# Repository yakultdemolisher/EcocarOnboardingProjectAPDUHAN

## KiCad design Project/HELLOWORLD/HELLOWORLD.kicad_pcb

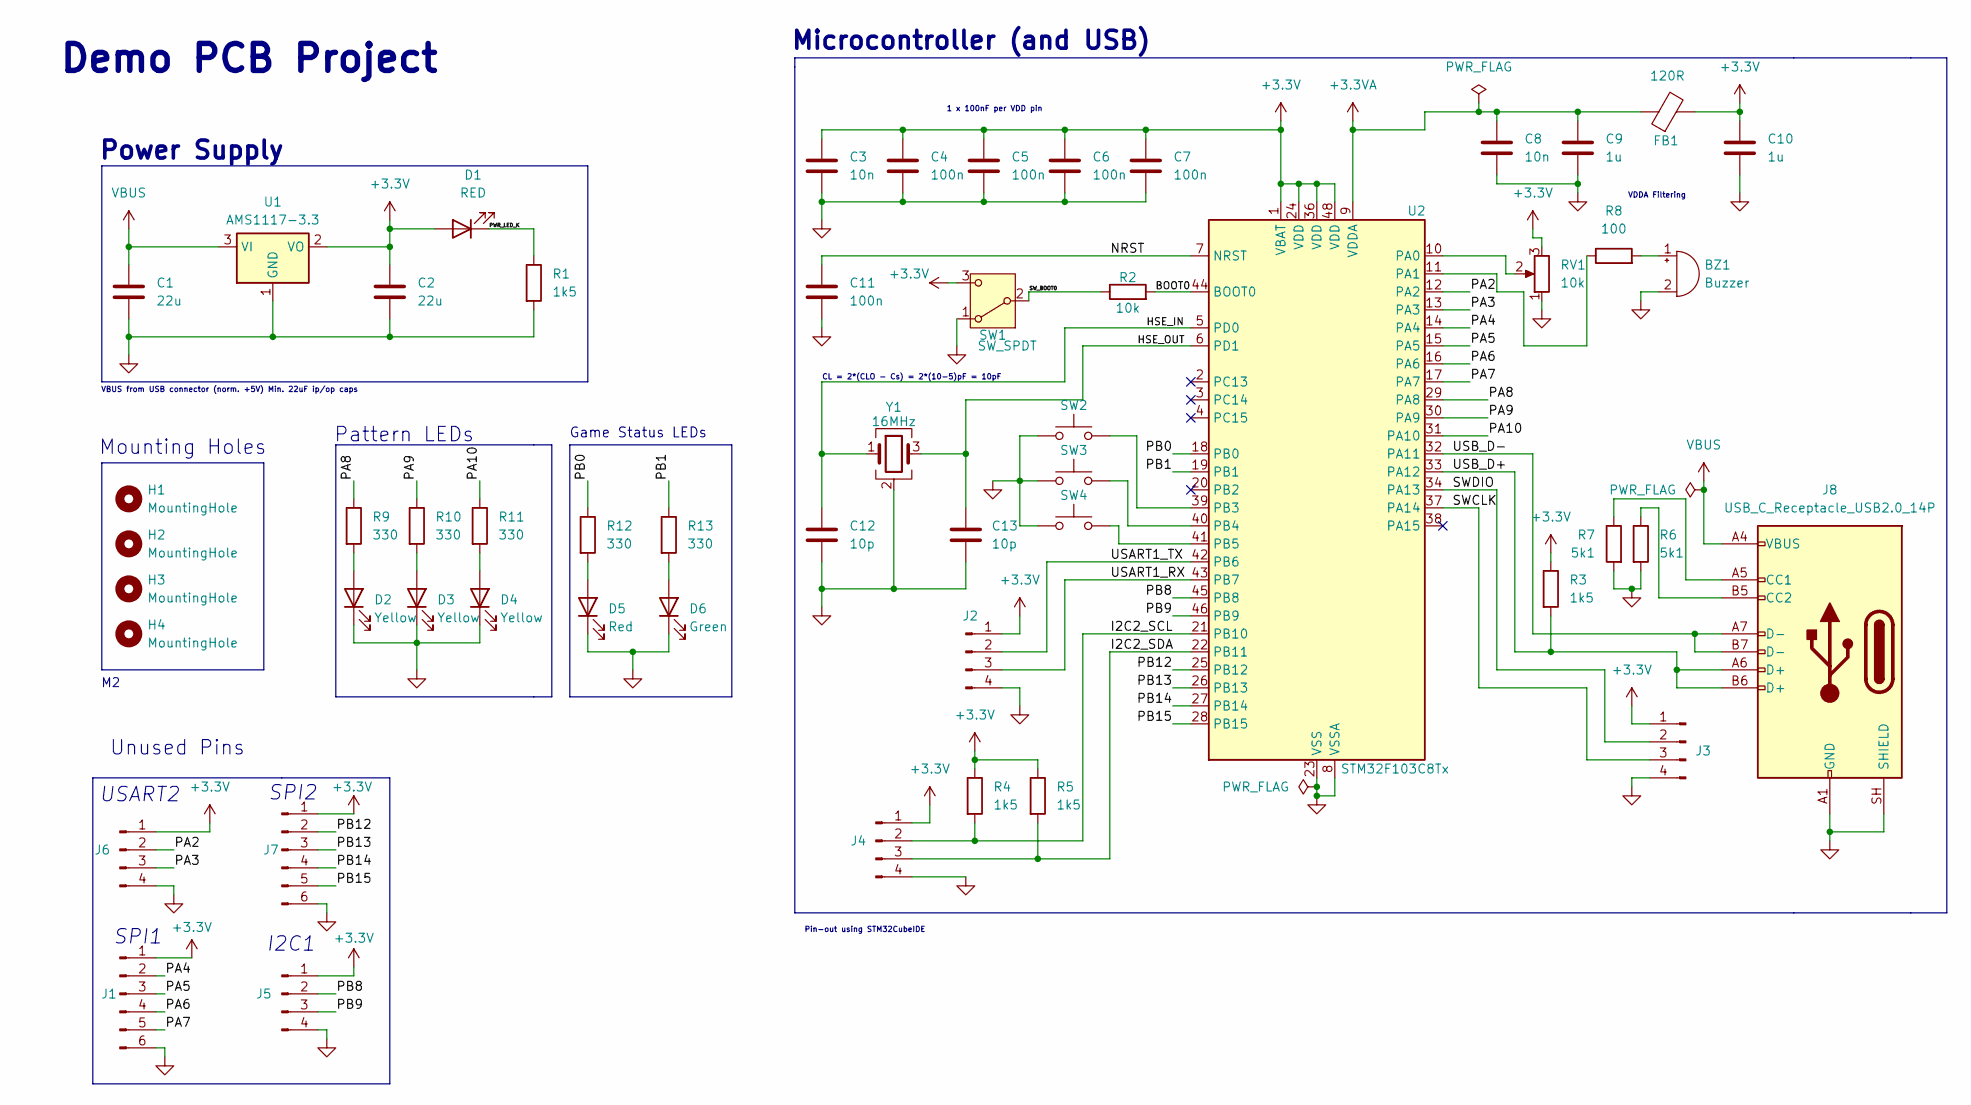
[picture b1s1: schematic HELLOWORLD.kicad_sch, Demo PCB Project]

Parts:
BZ1: Buzzer; Buzzer_12x9.5RM7.6
C1, C2: 22u; C_0805_2012Metric
C3, C8: 10n; C_0603_1608Metric
C4, C5, C6, C7, C11: 100n; C_0603_1608Metric
C9, C10: 1u; C_0603_1608Metric
C12, C13: 10p; C_0603_1608Metric
D1: RED; LED_0603_1608Metric
D2, D3, D4: Yellow; LED_0603_1608Metric
D5: Red; LED_0603_1608Metric
D6: Green; LED_0603_1608Metric
FB1: 120R; L_0603_1608Metric
H1, H2, H3, H4: MountingHole; MountingHole_2.2mm_M2
J1, J7: Conn_01x06_Pin; PinHeader_1x06_P2.54mm_Vertical
J2, J3, J4, J5, J6: Conn_01x04_Pin; PinHeader_1x04_P2.54mm_Vertical
J8: USB_C_Receptacle_USB2.0_14P; USB_C_Receptacle_GCT_USB4105-xx-A_16P_TopMnt_Horizontal
R1, R3, R4, R5: 1k5; R_0603_1608Metric
R2: 10k; R_0603_1608Metric
R6, R7: 5k1; R_0603_1608Metric
R8: 100; R_0603_1608Metric
R9, R10, R11, R12, R13: 330; R_0603_1608Metric
RV1: 10k; Potentiometer_Alps_RK09K_Single_Vertical
SW1: SW_SPDT; SW_SPDT_PCM12
SW2, SW3, SW4: SW_Push; SW_PUSH_6mm
U1: AMS1117-3.3; SOT-223-3_TabPin2
U2: STM32F103C8Tx; LQFP-48_7x7mm_P0.5mm
Y1: 16MHz; Crystal_SMD_3225-4Pin_3.2x2.5mm

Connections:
+3.3V: C2.1, C3.1, C4.1, C5.1, C6.1, C7.1, C10.1, D1.2 (A), FB1.2, J1.1, J2.1, J3.1, J4.1, J5.1, J6.1, J7.1, R3.1, R4.1, R5.1, RV1.3, SW1.3 (C), U1.2 (VO), U2.1 (VBAT), U2.24 (VDD), U2.36 (VDD), U2.48 (VDD)
+3.3VA: C8.1, C9.1, FB1.1, U2.9 (VDDA)
/BOOT0: R2.2, U2.44 (BOOT0)
/HSE_IN: C12.1, U2.5 (PD0), Y1.1
/HSE_OUT: C13.1, U2.6 (PD1), Y1.3
/I2C2_SCL: J4.2, R4.2, U2.21 (PB10)
/I2C2_SDA: J4.3, R5.2, U2.22 (PB11)
/NRST: C11.1, U2.7 (NRST)
/PA2: J6.2, U2.12 (PA2)
/PA3: J6.3, U2.13 (PA3)
/PA4: J1.2, U2.14 (PA4)
/PA5: J1.3, U2.15 (PA5)
/PA6: J1.4, U2.16 (PA6)
/PA7: J1.5, U2.17 (PA7)
/PA8: R9.1, U2.29 (PA8)
/PA9: R10.1, U2.30 (PA9)
/PA10: R11.1, U2.31 (PA10)
/PB0: R12.1, U2.18 (PB0)
/PB1: R13.1, U2.19 (PB1)
/PB8: J5.2, U2.45 (PB8)
/PB9: J5.3, U2.46 (PB9)
/PB12: J7.2, U2.25 (PB12)
/PB13: J7.3, U2.26 (PB13)
/PB14: J7.4, U2.27 (PB14)
/PB15: J7.5, U2.28 (PB15)
/PWR_LED_K: D1.1 (K), R1.1
/SWCLK: J3.3, U2.37 (PA14)
/SWDIO: J3.2, U2.34 (PA13)
/SW_BOOT0: R2.1, SW1.2 (B)
/USART1_RX: J2.3, U2.43 (PB7)
/USART1_TX: J2.2, U2.42 (PB6)
/USB_D+: J8.A6 (D+), J8.B6 (D+), R3.2, U2.33 (PA12)
/USB_D-: J8.A7 (D-), J8.B7 (D-), U2.32 (PA11)
GND: BZ1.2 (-), C1.2, C2.2, C3.2, C4.2, C5.2, C6.2, C7.2, C8.2, C9.2, C10.2, C11.2, C12.2, C13.2, D2.1 (K), D3.1 (K), D4.1 (K), D5.1 (K), D6.1 (K), J1.6, J2.4, J3.4, J4.4, J5.4, J6.4, J7.6, J8.A1 (GND), J8.A12 (GND), J8.B1 (GND), J8.B12 (GND), J8.SH (SHIELD), R1.2, R6.2, R7.2, RV1.1, SW1.1 (A), SW2.1, SW3.1, SW4.1, U1.1 (GND), U2.8 (VSSA), U2.23 (VSS), U2.35 (VSS), U2.47 (VSS), Y1.2 (G), Y1.4 (G)
unnamed: BZ1.1 (+), R8.2
unnamed: D2.2 (A), R9.2
unnamed: D3.2 (A), R10.2
unnamed: D4.2 (A), R11.2
unnamed: D5.2 (A), R12.2
unnamed: D6.2 (A), R13.2
unnamed: J8.A5 (CC1), R7.1
unnamed: J8.B5 (CC2), R6.1
unnamed: RV1.2, U2.10 (PA0)
unnamed: R8.1, U2.11 (PA1)
unnamed: SW2.2, U2.39 (PB3)
unnamed: SW3.2, U2.40 (PB4)
unnamed: SW4.2, U2.41 (PB5)
VBUS: C1.1, J8.A4 (VBUS), J8.A9 (VBUS), J8.B4 (VBUS), J8.B9 (VBUS), U1.3 (VI)

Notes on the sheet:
SPI2
Mounting Holes
Unused Pins
VBUS from USB connector (norm. +5V) Min. 22uF ip/op caps
1 x 100nF per VDD pin
SPI1
Pattern LEDs
Pin-out using STM32CubeIDE
Game Status LEDs
VDDA Filtering
I2C1
Power Supply
Demo PCB Project
Microcontroller (and USB)
USART2
CL = 2*(CLO - Cs) = 2*(10-5)pF = 10pF

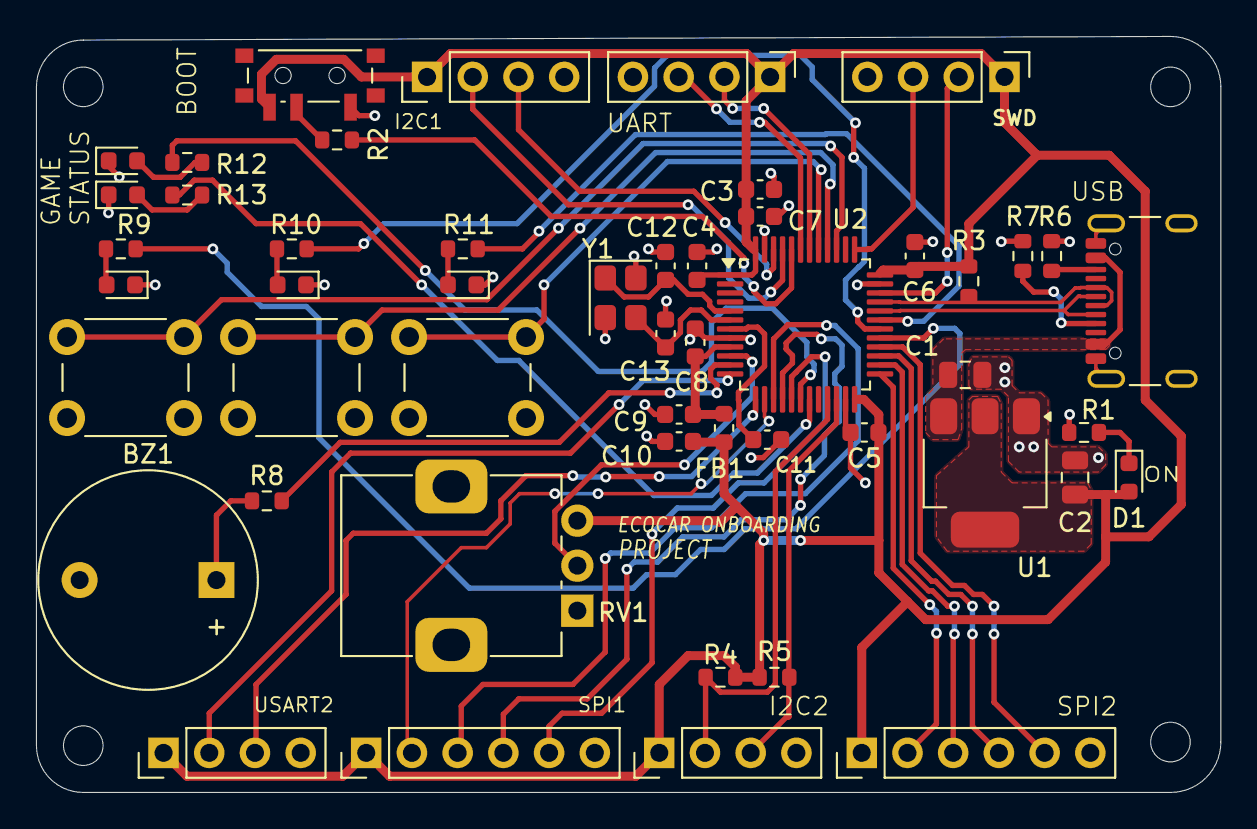
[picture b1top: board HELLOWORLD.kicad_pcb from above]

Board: 2 copper layers, 65.8 x 42.0 mm, 54 parts (0 on the bottom side), 48 nets.

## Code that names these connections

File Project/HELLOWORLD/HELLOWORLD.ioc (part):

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Mcu.Name=STM32F103C(8-B)Tx
Mcu.Package=LQFP48
Mcu.UserName=STM32F103C8Tx
PA11.Mode=Device
PA11.Signal=USB_DM
PA12.Mode=Device
PA12.Signal=USB_DP
PA13.Mode=Serial_Wire
PA13.Signal=SYS_JTMS-SWDIO
PA14.Mode=Serial_Wire
PA14.Signal=SYS_JTCK-SWCLK
PB10.Mode=I2C
PB10.Signal=I2C2_SCL
PB11.Mode=I2C
PB11.Signal=I2C2_SDA
PB6.Mode=Asynchronous
PB6.Signal=USART1_TX
PB7.Mode=Asynchronous
PB7.Signal=USART1_RX
PD0-OSC_IN.Mode=HSE-External-Oscillator
PD0-OSC_IN.Signal=RCC_OSC_IN
PD1-OSC_OUT.Mode=HSE-External-Oscillator
PD1-OSC_OUT.Signal=RCC_OSC_OUT
board=custom
